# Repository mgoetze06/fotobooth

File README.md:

# Fotobooth
Fotobooth is a python script running on a raspberry pi, controlling a Canon DSLR 1000D through gphoto2. Users can trigger the camera through a footswitch.

 Files for the background lights and nerdfacts sign can be found [here](/cad/).

# Webserver
Raspberry PI wlan interface is used to serve as a local Access Point. This wlan interface is used to access a local webserver running Flask and SocketIO. The main script [fotobooth.py](/fotobooth.py) launches the seperate .py script [fotobooth_webserver.py](/webserver/fotobooth_webserver_flask.py) in a subprocess. This is a WIP as the better approach is to use a standard apache-webserver with a WSGI for this. Anyway the locally hosted website is used to interact with the server/fotobooth without the need of a keyboard.

currently implemented:
1) display amount of photos, collages, time
2) display available storage, cpu, cpu temperature
3) set server time
4) shutdown/reboot server
5) download latest image
6) download all images as zip

# Computer Vision and Machine Learning
The fotobooth was part of an educational project at the Leipzig University of Applied Sciences (HTWK Leipzig). The folder [cvml](/cvml/) contains all scripts and notebooks developed during the project. The whole project relies heavily on opencv for python.
>https://pypi.org/project/opencv-python/

The cvml-project consists of two seperate parts:
1) hand detection and gesture recognition (mediapipe + tensorflow lite)
2) face (and object) detection (opencv cascade classifier)

## Mediapipe hand detection
The project uses the mediapipe framework from google to detect hand landmarks on an image. It returns an 1x21x2 Array containing the position of finger joints and finger tips in the image.

> https://google.github.io/mediapipe/solutions/hands.html

## Tensorflow Gesture Recognition
The landmarks that were detected by mediapipe are processed by a tensorflow lite model to recognize the gestures "thumbs up" and "thumbs down". The model was found on the blog:
> https://techvidvan.com/tutorials/hand-gesture-recognition-tensorflow-opencv/

and was converted from saved_model.pb to handgestures.tflite using the Tensorflow Model Converter:

> https://www.tensorflow.org/lite/models/convert/convert_models#python_api

## Face and Object Detection with Cascade Classifier
To postprocess the images taken in the fotobooth a cascade classifier was used to detect faces in images.
> face_cas = cv2.CascadeClassifier(cv2.data.haarcascades + 'haarcascade_frontalface_default.xml')

While giving acceptable results on normal images without any accessories, the results with people wearing big glasses were upgradable.
Therefore a custom cascade classifier was trained to detect the "Big Glasses" in images. The application to train the classifier is:

> https://amin-ahmadi.com/cascade-trainer-gui/

The following image of big glasses was detected with [big_glasses_classifier_5](/cvml/big_glasses_classifier_5.xml).

> sample resolution 150x150 <br/>
> max_scale = 1.2 <br/>
> min_neigh = 5 <br/>

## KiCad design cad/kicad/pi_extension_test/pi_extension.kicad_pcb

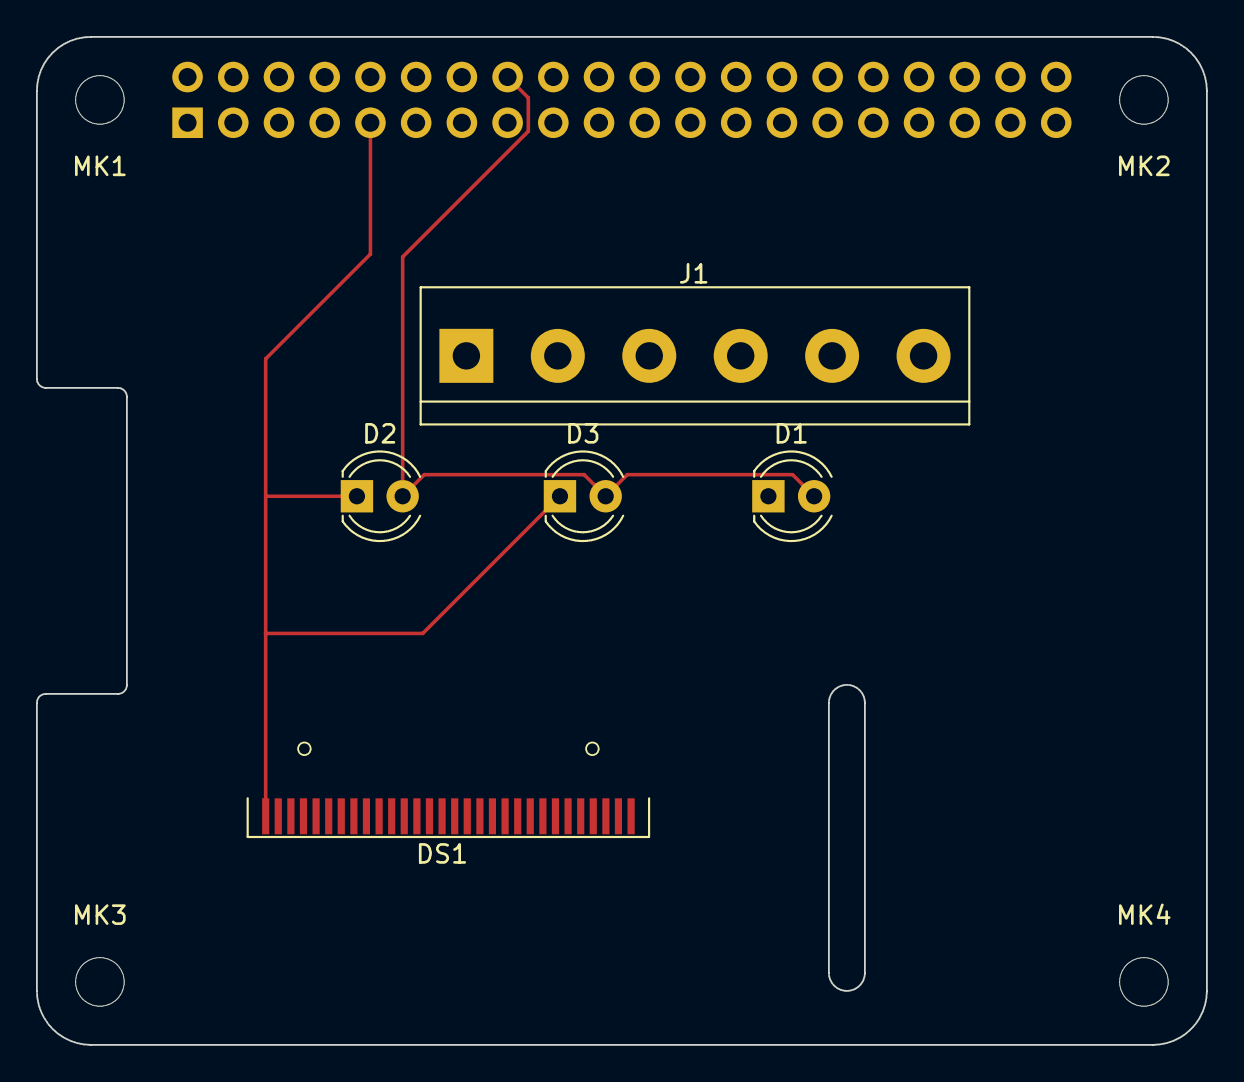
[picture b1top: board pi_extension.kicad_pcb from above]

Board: 2 copper layers, 65.0 x 56.0 mm, 10 parts (1 on the bottom side), 6 nets.

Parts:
D1, D2, D3: LED; LED_D4.0mm
DS1: OLED-128O064D
J1: Conn_01x10_Male; TerminalBlock_bornier-6_P5.08mm
MK1, MK2, MK3, MK4: M2.5; MountingHole_2.7mm_M2.5
P1: Conn_02x20_Odd_Even; PinSocket_2x20_P2.54mm_Vertical

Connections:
+3V3: P1.1, P1.17
+5V: P1.2, P1.4
/GPIO23(GEN4): D1.2 (A), D2.2 (A), D3.2 (A), P1.16
GND: D1.1 (K), D2.1 (K), D3.1 (K), DS1.1 (GND), DS1.30 (GND), P1.6, P1.9, P1.14, P1.20, P1.25, P1.30, P1.34, P1.39
unnamed: DS1.8 (VSS), J1.1
unnamed: DS1.29 (VLSS), J1.2

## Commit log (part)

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2021-04-19 initial file upload
2022-05-24 Erstellt mit Colaboratory
2022-05-24 crop original image to one face
2022-05-24 crop to original image single face
2022-05-24 multiple faces in images
2022-05-24 multiple faces plot
2022-05-24 smile classifier
2022-05-24 detecting all faces
2022-05-24 convert to script comment
2022-05-27 started gesture detection with tensorflow
2022-05-28 detecting one hand, problem with detecting multiple hands
2022-05-30 detecting multiple hands
2022-05-30 small optim.
2022-05-30 gphoto2 with python and dslr
2022-06-01 gphoto2 with python and dslr and cv2 face detection
2022-06-15 added cad files for fotobox sign
2022-06-15 cad fotobox sign with parametric cadquery
2022-06-15 cad fotobox sign, text size transformation started with Pillow font.getsize
2022-06-16 calculate thumb orientation with distance; without model prediction --> no tensorflow needed
2022-06-16 folder management
2022-06-16 mediapipe hand detection without tensorflow, but with gphoto2 dslr support (preview images)
2022-06-21 started hex points array calculation for displaying in gallery mode in post processing of face recognition
2022-06-30 added readme image
2022-07-18 face detection as a function to check folder. Collage for displaying faces in hex format working. TODO: new Collage with fewer but bigger faces
2022-07-19 read hex points from csv
2022-07-21 todo cascade classifier for object detection
2022-07-22 Todo added
2022-07-25 big hexagons for selection of faces
2022-07-25 bigger hexagons for classified faces, background generated for classifying with thumbs up/down
2022-07-26 classify faces and move them to pos/neg directory;create face collages from pos directory; functions created from cell content
2022-07-27 cv2 test to rescale and show images on fullscreen; also showing two images after eachother like in a gallery
2022-07-29 first test with template matching
2022-07-29 test of template matching
2022-08-01 mnist dataset with tensorflow and keras
2022-08-01 create data dir (gitignore)
2022-08-01 preparations for cascade classifier, creation of samples etc
2022-08-05 first try with big glasses classifier
2022-08-05 big glasses classifier working somehow
2022-08-05 big glasses classifier working with selected parameters on most images
2022-08-05 big glasses classifier working with selected parameters on most images; cleaned notebook
2022-08-10 rotate pos samples by degree, replace black background with random position from negative sample--> create more samples for gui trainer (cascade)
2022-08-31 added animation between two images (slide new images from right to left)
2022-09-01 started fotobooth rework with cv2 and a seperate handler. no PIL anymore
2022-09-02 frame handler and next frame operation in seperate threads
2022-09-02 added mouse callback on leftclick; Todo: there is an image showing between mouseclick and animation/newimage
2022-09-05 started to write functions for raspberry out of notebook
2022-09-05 added todo
2022-09-05 created functions for dslr control on raspberry
2022-09-07 pi tests with tflite and model conversion
2022-09-09 pi and pc test on up and down samples, loop preview and detection on dslr
2022-09-11 prepare image loop for classification without model. Todo: test with model output
2022-09-11 overlay png images of thumbs up and down
2022-09-12 classify faces with hand gestures
2022-09-13 prepare for metrics calculation with test and validation data
2022-09-13 files and data array added
2022-09-14 pi metrics test on test dataset (140samples of binary classes thumbs up and thumbs down)
2022-09-14 started multiprocessing way of displaying and handling new frames using multiprocessing BaseManager
2022-09-15 mouse click event working in multiprocessing
2022-09-21 pi tests; prepare presentation
2022-09-27 cvml project completed. Starting to rework fotobooth
2022-09-29 cvml project done. folder management
2022-09-29 results folder, hand gestures tensorflow model, folder management
2022-10-09 added error detection, fixed imglist with directories
2022-10-09 create collage from detections
2022-10-09 cascade detection started for background use in collage process
2022-12-03 added webserver testing for handling fotobooth script withoud keyboard and from local ip address
2022-12-04 added index.html on branch website
2022-12-04 checking state of fotobooth
2022-12-12 moved kicad template
2022-12-12 added python checker, needs further testing
2023-05-23 Added Website
2023-05-29 feat-website: added python server support for other file types than html (http mimetypes)
2023-06-07 feat-blurred: added basic calculation to detect blurred images
2023-06-07 feat-blurred: added notebook
2023-06-07 feat blurred: notebook added
2024-08-14 ip address added to oled display
2024-08-14 try except in newImg()
2024-08-14 reuse old folder if younger than 12 hours
2024-08-14 detectionToCollage
2024-08-14 gitignore
2024-08-14 tab fix
2024-08-19 fix wrong collage base image
2024-08-20 added new stripe image to repo
2024-08-20 updated requirements and single collage mode
2024-08-20 added example collage
2024-08-21 simple website to choose color and write to textfile
2024-08-22 farbe wird in textdatei gespeichert
2024-08-22 onchange submit and read/write photocount to file
2024-08-23 webserver added as subprocess; general program more stable
2024-08-24 increased color picker size
2024-09-03 test webserver with download option
2024-09-04 umstellung auf webserver flask
2024-09-04 anpassung farbe und größe der elemente
2024-09-05 index html from template
2024-09-05 download zip and download single file
2024-09-06 flexbox test
2024-09-07 flexbox test for project konzerterinnerungen
2024-09-11 umstellung auf klassische tiles mit flexbox
2024-09-15 basic button function
2024-09-15 button style
2024-09-15 farbe als hintergrund des elements
2024-09-15 changes after test on real pi
2024-09-16 umbau auf socketio für datenaustausch
2024-09-19 disk usage and time in websocket
2024-09-20 stats added and styled
2024-09-20 small change
2024-09-20 eventname
2024-09-26 umstellung von alert auf custom card für reboot und shutdown
2024-09-26 hintergrund blurred bei infomodal
2024-09-26 socket emit not working in flask route
2024-09-26 webserver nach test auf PI
2024-09-26 zeiten angepasst; serverzeit setzbar; download mit zwischenanzeige
2024-10-02 collage test read background color from file
2024-10-03 more types of collages
2024-10-04 added support for background color
2024-10-04 upload collage template created; no new folders on reboot
2024-10-14 robuster zugriff auf listen; oled text gefixt
2024-11-01 liveview test before taking a photo
2024-11-04 test mit autofocus im liveview mode, leider mit wenig erfolg
2024-11-05 try catch added
2024-11-07 erster versuch mit python-gphoto implementierung in fotobooth.py
2024-11-07 countdown added with seperate event
2025-03-31 added basic usb webcam stream
2025-03-31 basic overlay with tkinter; TODO Main integration
2025-03-31 place in widget using tk
2025-04-22 countdown über webserver einschaltbar
2025-04-23 verzögerung countdown durch webserver; slider not working
2025-05-21 fixed countdown from webserver with two buttons
2026-02-06 added overlay integration and focus fallback image
2026-05-18 script hardening
2026-05-18 read overlay fix
2026-05-18 reverting changes to captureImage
2026-05-20 fixed empty collage
2026-05-20 changed backup and zip in multiple files
2026-05-20 added last image node
2026-05-20 added switch to random image
2026-05-20 added slider to control intervall and style to transparent
2026-06-29 added gui event loop and restarting service routine
